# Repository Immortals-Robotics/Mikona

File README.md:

# ImmortalsMikona
Immortals kicker board known as Mikona

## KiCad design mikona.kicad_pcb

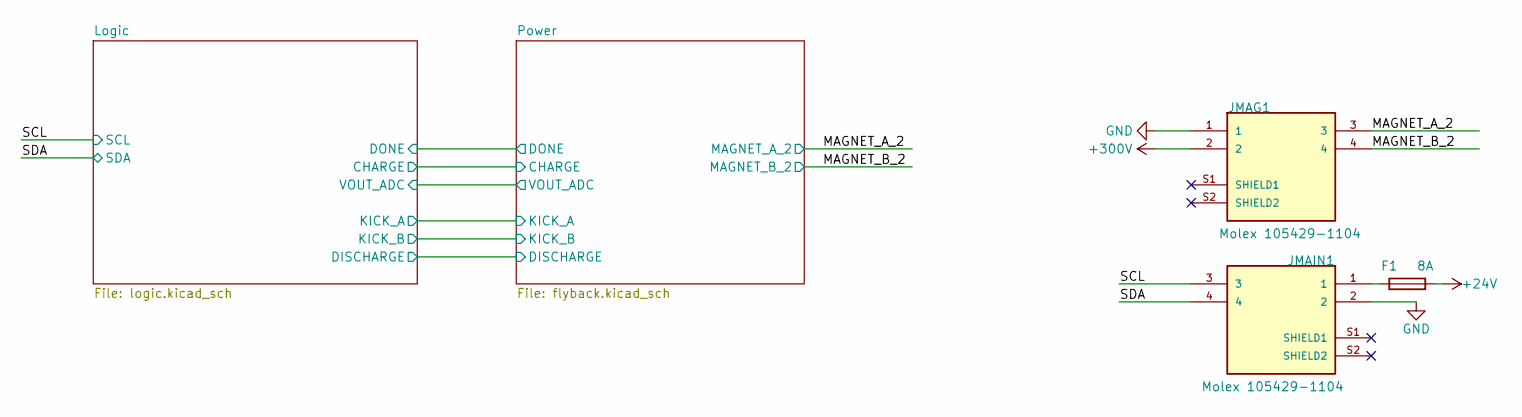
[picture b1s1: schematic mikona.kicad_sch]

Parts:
F1: 8A; Fuse_0603_1608Metric; MPN SF-0603SA800M-2
JMAG1: Molex 105429-1104; MOLEX_1054291104; MPN 1054291104
JMAIN1: Molex 105429-1104; MOLEX_1054291104; MPN 1054291104

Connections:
+24V: F1.2; also elsewhere on the board
/MAGNET_A_2: JMAG1.3; also elsewhere on the board
/MAGNET_B_2: JMAG1.4; also elsewhere on the board
/SCL: JMAIN1.3; also elsewhere on the board
/SDA: JMAIN1.4; also elsewhere on the board
GND: JMAG1.1, JMAIN1.2; also elsewhere on the board
unnamed: F1.1, JMAIN1.1
VDC: JMAG1.2; also elsewhere on the board

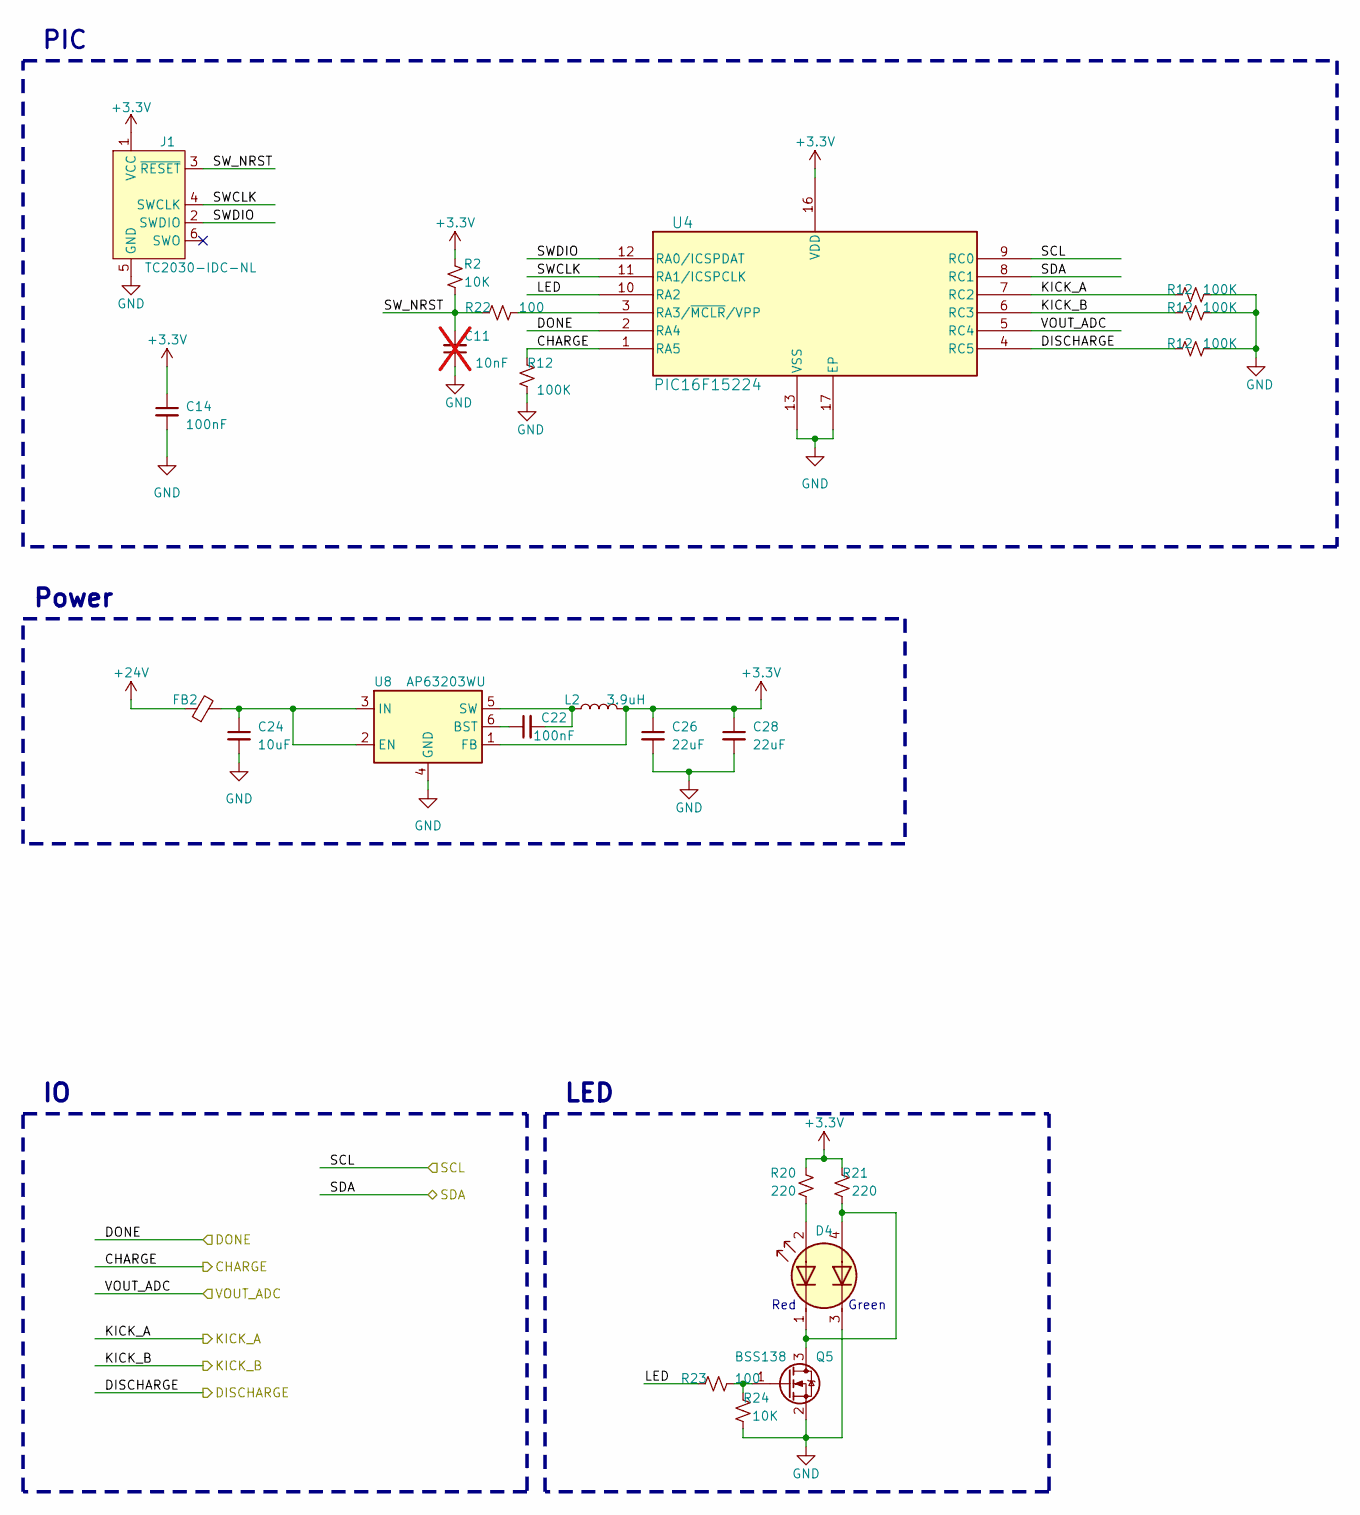
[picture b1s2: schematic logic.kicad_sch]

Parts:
C11: 10nF; C_0402_1005Metric; MPN 885012205067; not fitted
C14, C22: 100nF; C_0402_1005Metric; MPN GRM155R71H104KE14J
C24: 10uF; C_0603_1608Metric; MPN GRM188R6YA106MA73D
C26, C28: 22uF; C_0805_2012Metric; MPN CL21A226MPQNNNE
D4: LED Dual; LED_Avago_PLCC4_3.2x2.8mm_CW; MPN LTST-E682KRKGWT
FB2: FerriteBead_Small; R_0603_1608Metric; MPN BLM18KG101TN1D
J1: TC2030-IDC-NL; Tag-Connect_TC2030-IDC-NL_2x03_P1.27mm_Vertical; MPN TC2030-IDC-NL
L2: 3.9uH; L_Bourns-SRN6028; MPN SRN6028C-3R9M
Q5: BSS138; SOT-23; MPN BSS138-7-F
R2, R24: 10K; R_0402_1005Metric; MPN RC1005F103CS
R12: 100K; R_0402_1005Metric; MPN WR04X1003FTL
R20, R21: 220; R_0402_1005Metric; MPN ERJ-U02F2200X
R22, R23: 100; R_0402_1005Metric; MPN ERJ-2RKF1000X
U4: PIC16F15224; VQFN-16-1EP_3x3mm_P0.5mm_EP1.1x1.1mm; MPN PIC16F15224-I/MG
U8: AP63203WU; TSOT-23-6; MPN AP63203WU-7

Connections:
+3.3V: C14.1, C26.1, C28.1, J1.1 (VCC), L2.2, R2.2, R20.2, R21.2, U4.16 (VDD), U8.1 (FB); also elsewhere on the board
+24V: FB2.1; also elsewhere on the board
/Logic/CHARGE: U4.1 (RA5); also elsewhere on the board
/Logic/DISCHARGE: U4.4 (RC5); also elsewhere on the board
/Logic/DONE: U4.2 (RA4); also elsewhere on the board
/Logic/KICK_A: U4.7 (RC2); also elsewhere on the board
/Logic/KICK_B: U4.6 (RC3); also elsewhere on the board
/Logic/LED: R23.2, U4.10 (RA2)
/Logic/SWCLK: J1.4 (SWCLK), U4.11 (RA1/ICSPCLK)
/Logic/SWDIO: J1.2 (SWDIO), U4.12 (RA0/ICSPDAT)
/Logic/SW_NRST: C11.2, J1.3 (~RESET), R2.1, R22.2
/Logic/VOUT_ADC: U4.5 (RC4); also elsewhere on the board
/SCL: U4.9 (RC0); also elsewhere on the board
/SDA: U4.8 (RC1); also elsewhere on the board
GND: C11.1, C14.2, C24.2, C26.2, C28.2, D4.3 (A2), J1.5 (GND), Q5.2 (S), R24.1, U4.13 (VSS), U4.17 (EP), U8.4 (GND); also elsewhere on the board
unnamed: D4.1 (A1), D4.4 (K2), Q5.3 (D), R21.1
unnamed: D4.2 (K1), R20.1
unnamed: Q5.1 (G), R23.1, R24.2
unnamed: R22.1, U4.3 (RA3/~MCLR/VPP)
unnamed: C22.1, U8.6 (BST)
unnamed: C24.1, FB2.2, U8.2 (EN), U8.3 (IN)
unnamed: C22.2, L2.1, U8.5 (SW)

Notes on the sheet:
Green
Red
Power
PIC
LED

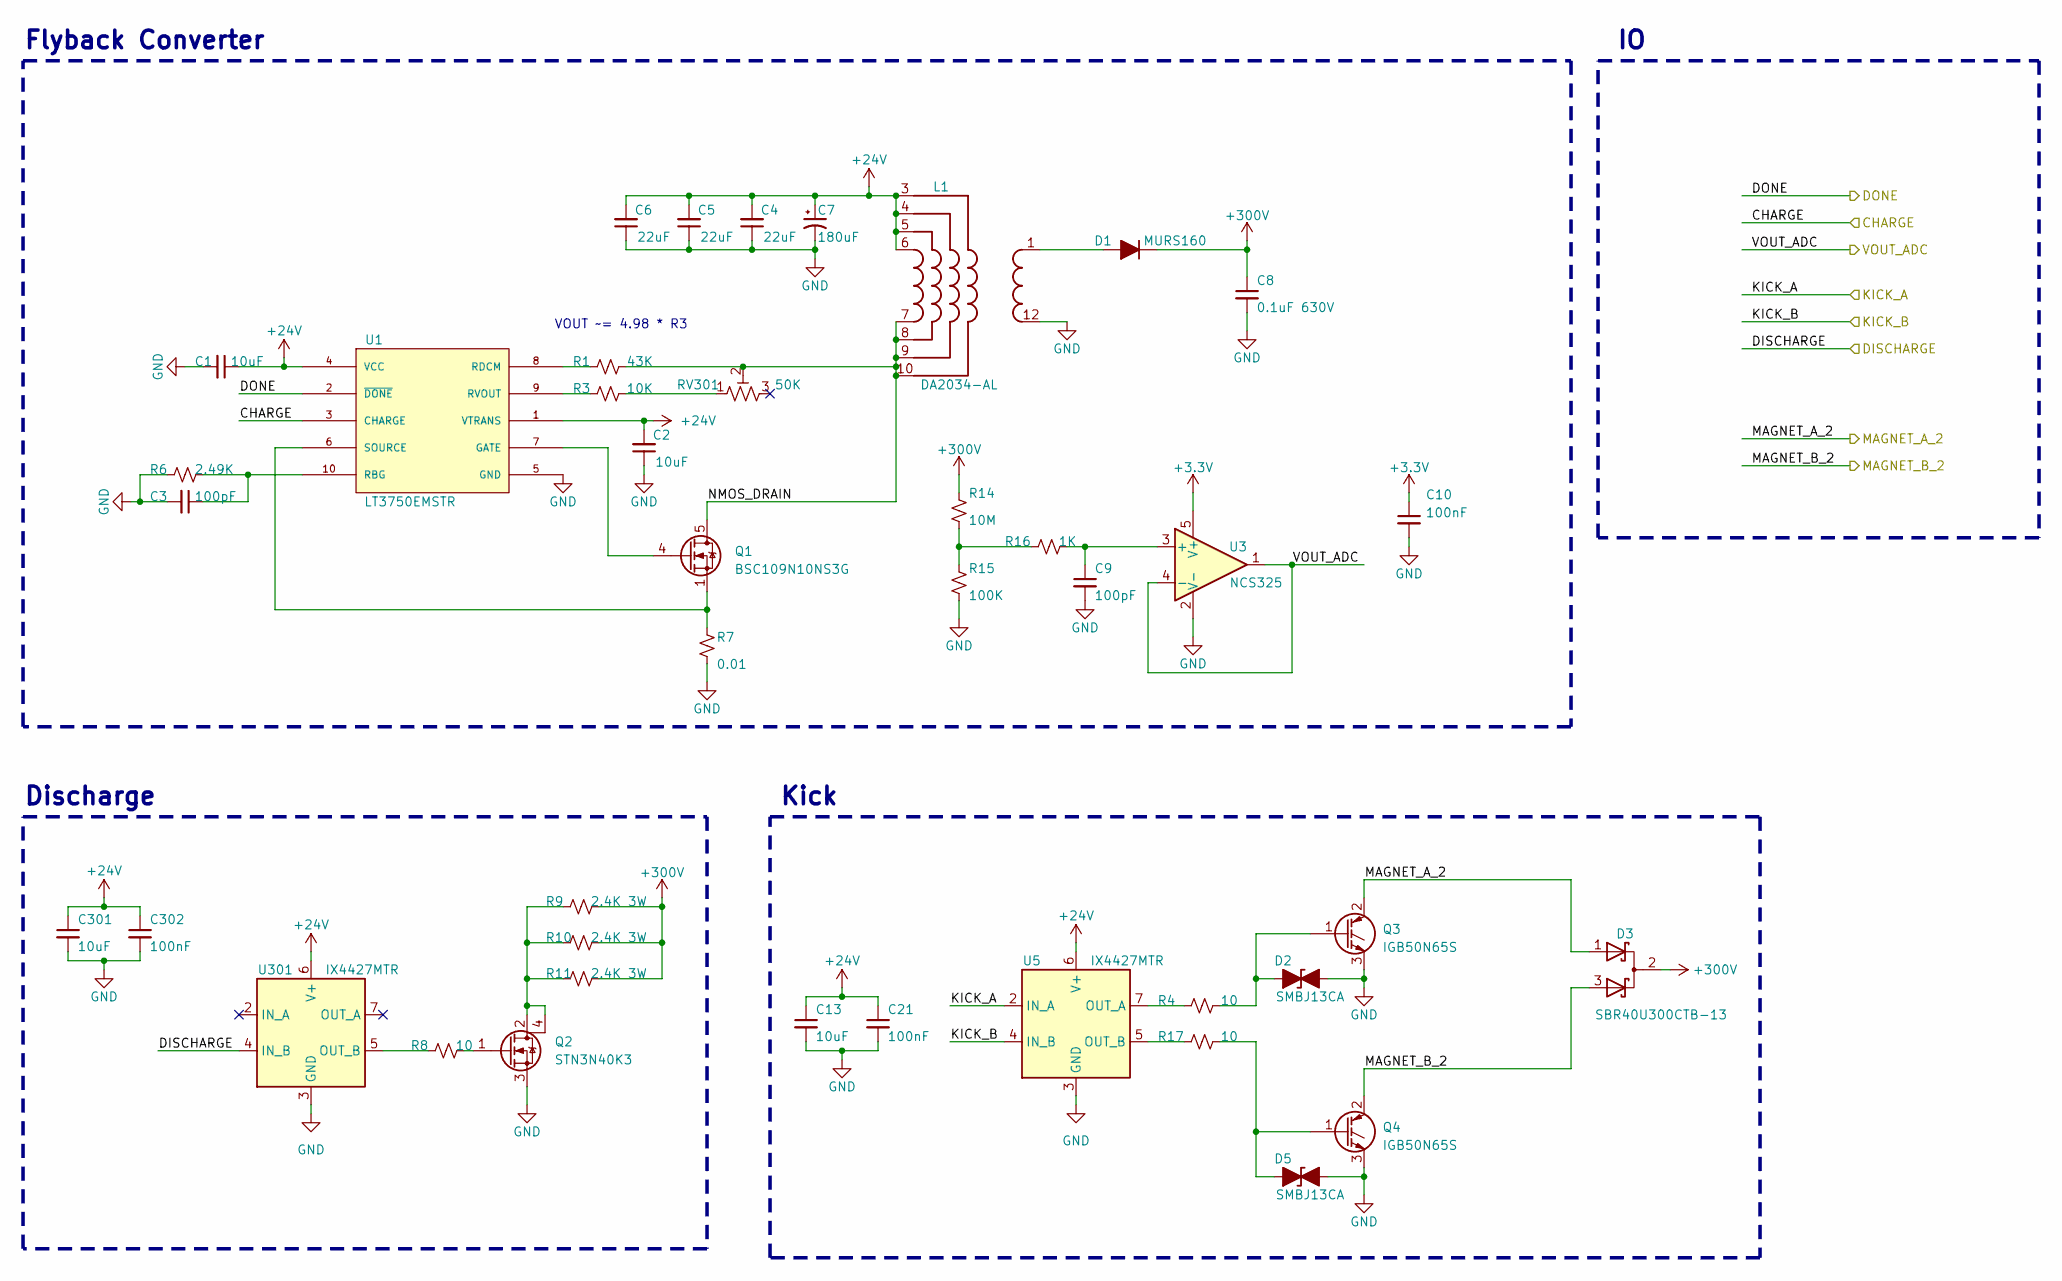
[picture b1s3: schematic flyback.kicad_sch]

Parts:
C1, C13, C301: 10uF; C_0805_2012Metric; MPN GRM21BR61H106KE43L
C2: 10uF; C_0603_1608Metric; MPN GRM188R6YA106MA73D
C3, C9: 100pF; C_0402_1005Metric; MPN 885012205055
C4, C5, C6: 22uF; C_1210_3225Metric; MPN GRM32ER71E226KE15L
C7: 180uF; CP_Elec_8x11.9; MPN 35SVPK180M
C8: 0.1uF 630V; C_1812_4532Metric; MPN C4532X7R2J104K230KA
C10, C21, C302: 100nF; C_0402_1005Metric; MPN GRM155R71H104KE14J
D1: MURS160; D_SMB; MPN MURS160A
D2, D5: SMBJ13CA; D_SMB; MPN SMBJ13CA-13-F
D3: SBR40U300CTB-13; TO-263-2; MPN SBR40U300CTB-13
L1: DA2034-AL; MPN DA2034-ALD
Q1: BSC109N10NS3G; TDSON-8-1; MPN BSC109N10NS3 G
Q2: STN3N40K3; SOT-223; MPN STN3N40K3
Q3, Q4: IGB50N65S; TO-263-2; MPN IGB50N65S5ATMA1
R1: 43K; R_0402_1005Metric; MPN CRCW040243K0JNED
R3: 10K; R_0402_1005Metric; MPN RC1005F103CS
R4, R8, R17: 10; R_0402_1005Metric; MPN ERJ-2RKF10R0X
R6: 2.49K; R_0402_1005Metric; MPN CR0402-FX-2491GLF
R7: 0.01; R_0805_2012Metric; MPN D1WKL0805MR010F-T5
R9, R10, R11: 2.4K 3W; R_2512_6332Metric; MPN 35222K4FT
R14: 10M; R_0603_1608Metric; MPN KTR03EZPF1005
R15: 100K; R_0402_1005Metric; MPN WR04X1003FTL
R16: 1K; R_0603_1608Metric; MPN RC0603FR-101KL
RV301: 50K; Potentiometer_Bourns_TC33X_Vertical; MPN TC33X-2-503E
U1: LT3750EMSTR; MSOP-10_MS; MPN LT3750EMS#TRPBF
U3: NCS325; SOT-23-5; MPN NCS325SN2T1G
U5, U301: IX4427MTR; DFN-8-1EP_3x3mm_P0.65mm_EP1.7x2.05mm; MPN IX4427MTR

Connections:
+3.3V: C10.1, U3.5 (V+); also elsewhere on the board
+24V: C1.1, C2.2, C4.2, C5.2, C6.2, C7.1, C13.1, C21.1, C301.1, C302.1, L1.3, L1.4, L1.5, L1.6, U1.1 (VTRANS), U1.4 (VCC), U5.6 (V+), U301.6 (V+); also elsewhere on the board
/Logic/CHARGE: U1.3 (CHARGE); also elsewhere on the board
/Logic/DISCHARGE: U301.4 (IN_B); also elsewhere on the board
/Logic/DONE: U1.2 (~DONE); also elsewhere on the board
/Logic/KICK_A: U5.2 (IN_A); also elsewhere on the board
/Logic/KICK_B: U5.4 (IN_B); also elsewhere on the board
/Logic/VOUT_ADC: U3.1, U3.4 (-); also elsewhere on the board
/MAGNET_A_2: D3.1 (K), Q3.2 (C); also elsewhere on the board
/MAGNET_B_2: D3.3 (K), Q4.2 (C); also elsewhere on the board
/Power/NMOS_DRAIN: L1.7, L1.8, L1.9, L1.10, Q1.5 (D), R1.1, RV301.2
GND: C1.2, C2.1, C3.2, C4.1, C5.1, C6.1, C7.2, C8.2, C9.2, C10.2, C13.2, C21.2, C301.2, C302.2, D2.2 (A2), D5.2 (A2), L1.12, Q2.3 (S), Q3.3 (E), Q4.3 (E), R6.2, R7.2, R15.2, U1.5 (GND), U3.2 (V-), U5.3 (GND), U301.3 (GND); also elsewhere on the board
unnamed: D1.2 (A), L1.1
unnamed: D2.1 (A1), Q3.1 (G), R4.1
unnamed: D5.1 (A1), Q4.1 (G), R17.1
unnamed: Q1.4 (G), U1.7 (GATE)
unnamed: Q2.2 (D), Q2.4 (D), R9.2, R10.2, R11.2
unnamed: Q2.1 (G), R8.1
unnamed: R3.1, RV301.1
unnamed: R14.2, R15.1, R16.2
unnamed: C3.1, R6.1, U1.10 (RBG)
unnamed: R1.2, U1.8 (RDCM)
unnamed: R3.2, U1.9 (RVOUT)
unnamed: Q1.1 (S), Q1.2 (S), Q1.3 (S), R7.1, U1.6 (SOURCE)
unnamed: C9.1, R16.1, U3.3 (+)
unnamed: R4.2, U5.7 (OUT_A)
unnamed: R17.2, U5.5 (OUT_B)
unnamed: R8.2, U301.5 (OUT_B)
VDC: C8.1, D1.1 (K), D3.2 (A), R9.1, R10.1, R11.1, R14.1; also elsewhere on the board

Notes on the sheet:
VOUT ~= 4.98 * R3
Kick
Flyback Converter
Discharge

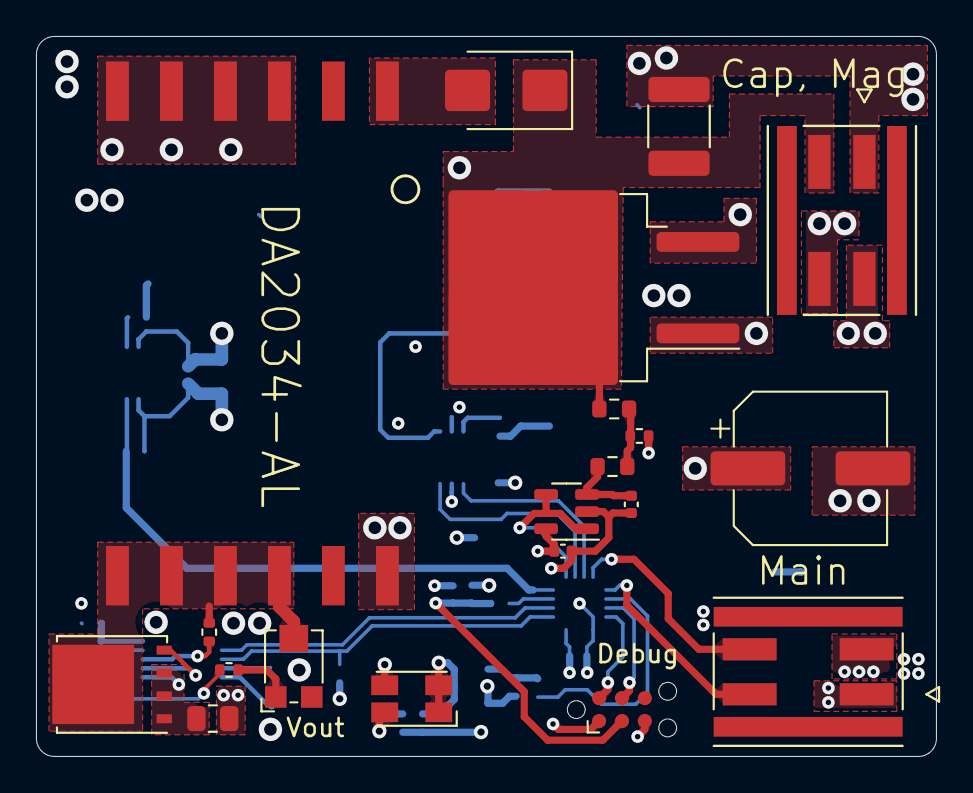
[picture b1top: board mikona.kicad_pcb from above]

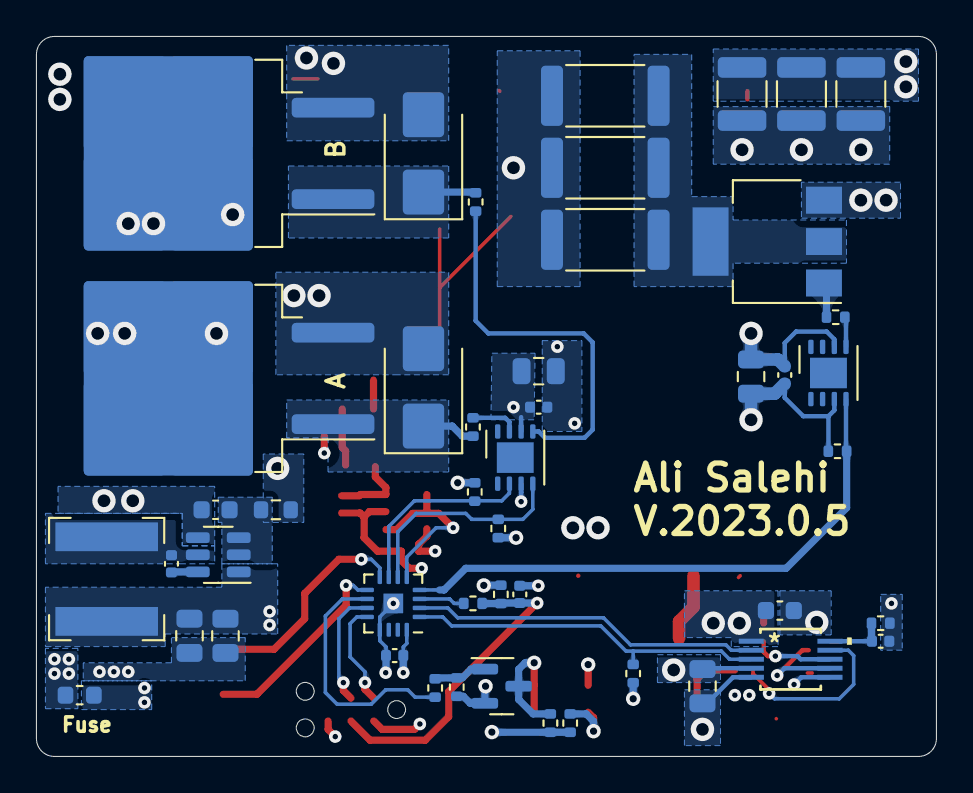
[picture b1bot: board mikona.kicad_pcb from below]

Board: 4 copper layers, 50.0 x 40.0 mm, 67 parts (47 on the bottom side), 43 nets.

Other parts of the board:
R5, R13, R18, R19: 100K; R_0402_1005Metric

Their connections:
/Logic/CHARGE: R19.2; also elsewhere on the board
/Logic/DISCHARGE: R18.2; also elsewhere on the board
/Logic/KICK_A: R5.2; also elsewhere on the board
/Logic/KICK_B: R13.2; also elsewhere on the board
GND: R5.1, R13.1, R18.1, R19.1; also elsewhere on the board

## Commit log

2023-03-02 Import the project from CircuitMaker.
2023-03-06 Cleanup the project after moving to KiCad.
2023-03-06 Add missing 3d models.
2023-03-17 Finish the layout, remove old routings, and setup internal planes.
2023-03-17 Finish the draft routing.
2023-03-17 Move a lot of vias out of pads as this is an expensive option when manufacturing the PCB.
2023-04-08 Add jlpcb rules and fix many violations.
2023-04-08 Move the flash mem to bottom layer, we're now error-free, yay :D
2023-04-10 Improve routing, almost there.
2023-04-12 Remove 2 unused tracks.
2023-04-12 Organize silkscreen and improve power layer.
2023-04-14 Improve regulator routing.
2023-04-14 Fix minimum via hole size violations.
2023-05-01 Update MPNs and add jlcpcb comments.
2023-05-02 Add teardrops and version text.
2023-05-28 Move from stm32 to pic16 and remove other unnecessary parts.
2023-05-28 Finish routing.
2023-05-28 Minor fixes to the PCB.
2023-05-28 Remove an unused config file.
2023-05-28 Use the correct package for 4427.
2023-06-09 Fix issues found during testing.
2023-06-09 Use parts similar to motor-driver where possible.
2023-06-09 Use parts similar to the main pcb where possible.
2023-06-09 Add missing MPNs.
2023-06-11 Change the parts that were not in stock.
2023-06-11 Apply the MPN changes to the PCB.
2023-06-11 Modify the ibom config.
